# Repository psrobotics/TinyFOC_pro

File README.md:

# TinyFOC_pro

<br><br>
<br>
<br>

<br><br>

* Compact brushless motor driver modified from [mit mini cheetah driver](https://github.com/bgkatz/3phase_integrated)
* 12 bit GMR-based encoder with MA710 or AS5047p
* CAN, hardware serial

Design file exported with [Autodesk EAGLE](https://www.autodesk.com/products/eagle/overview?term=1-YEAR&tab=subscription)

## License
MIT License

## Contact
* Shuang Peng, {shuangpe}@usc.edu

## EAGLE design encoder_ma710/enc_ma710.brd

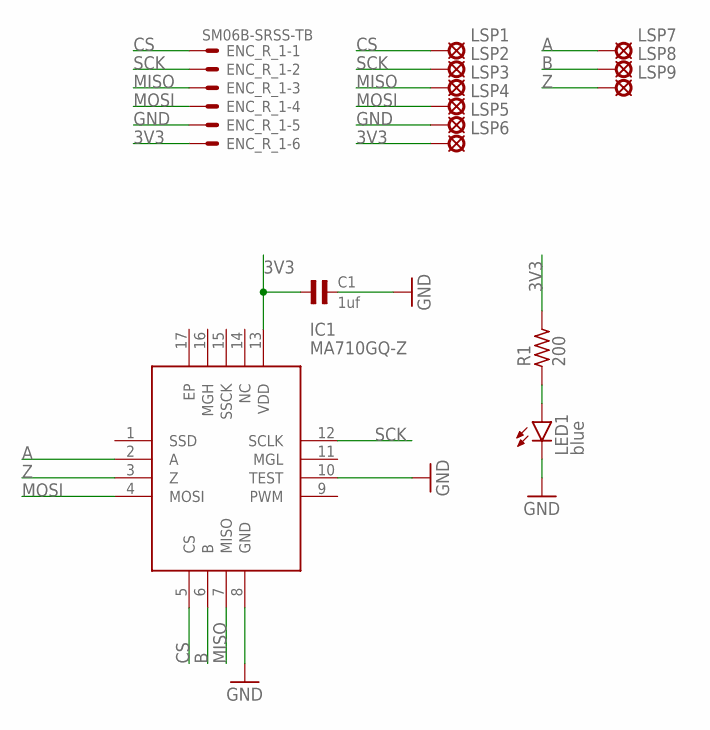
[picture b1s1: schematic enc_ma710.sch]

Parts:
C1: 1uf; 0603
ENC_R_1: SM06B-SRSS-TB
IC1: MA710GQ-Z; QFN50P300X300X100-17N
LED1: blue; SML0603
LSP1, LSP2, LSP3, LSP4, LSP5, LSP6, LSP7, LSP8, LSP9: LSP10
R1: 200; R0603

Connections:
3V3: C1.1, ENC_R_1.6, IC1.13 (VDD), LSP6.MP, R1.2
A: IC1.2 (A), LSP7.MP
B: IC1.6 (B), LSP8.MP
CS: ENC_R_1.1, IC1.5 (CS), LSP1.MP
GND: C1.2, ENC_R_1.5, IC1.8 (GND), IC1.10 (TEST), LED1.C, LSP5.MP
MISO: ENC_R_1.3, IC1.7 (MISO), LSP3.MP
MOSI: ENC_R_1.4, IC1.4 (MOSI), LSP4.MP
unnamed: LED1.A, R1.1
SCK: ENC_R_1.2, IC1.12 (SCLK), LSP2.MP
Z: IC1.3 (Z), LSP9.MP

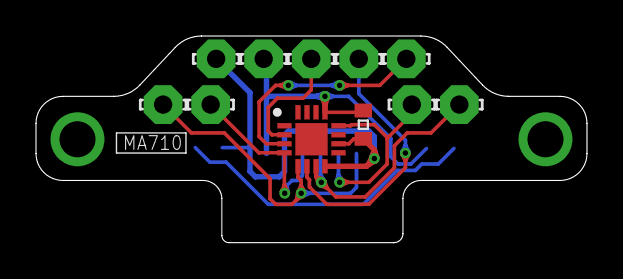
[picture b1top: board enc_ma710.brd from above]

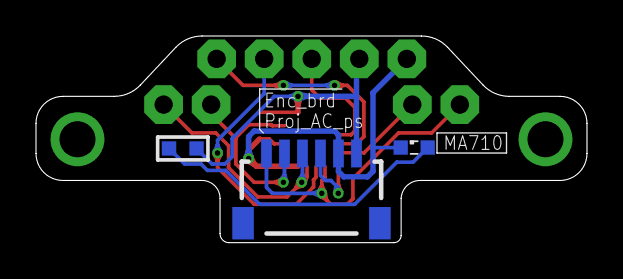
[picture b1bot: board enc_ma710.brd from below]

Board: 2 copper layers, 30.6 x 11.5 mm, 14 parts (3 on the bottom side), 10 nets.

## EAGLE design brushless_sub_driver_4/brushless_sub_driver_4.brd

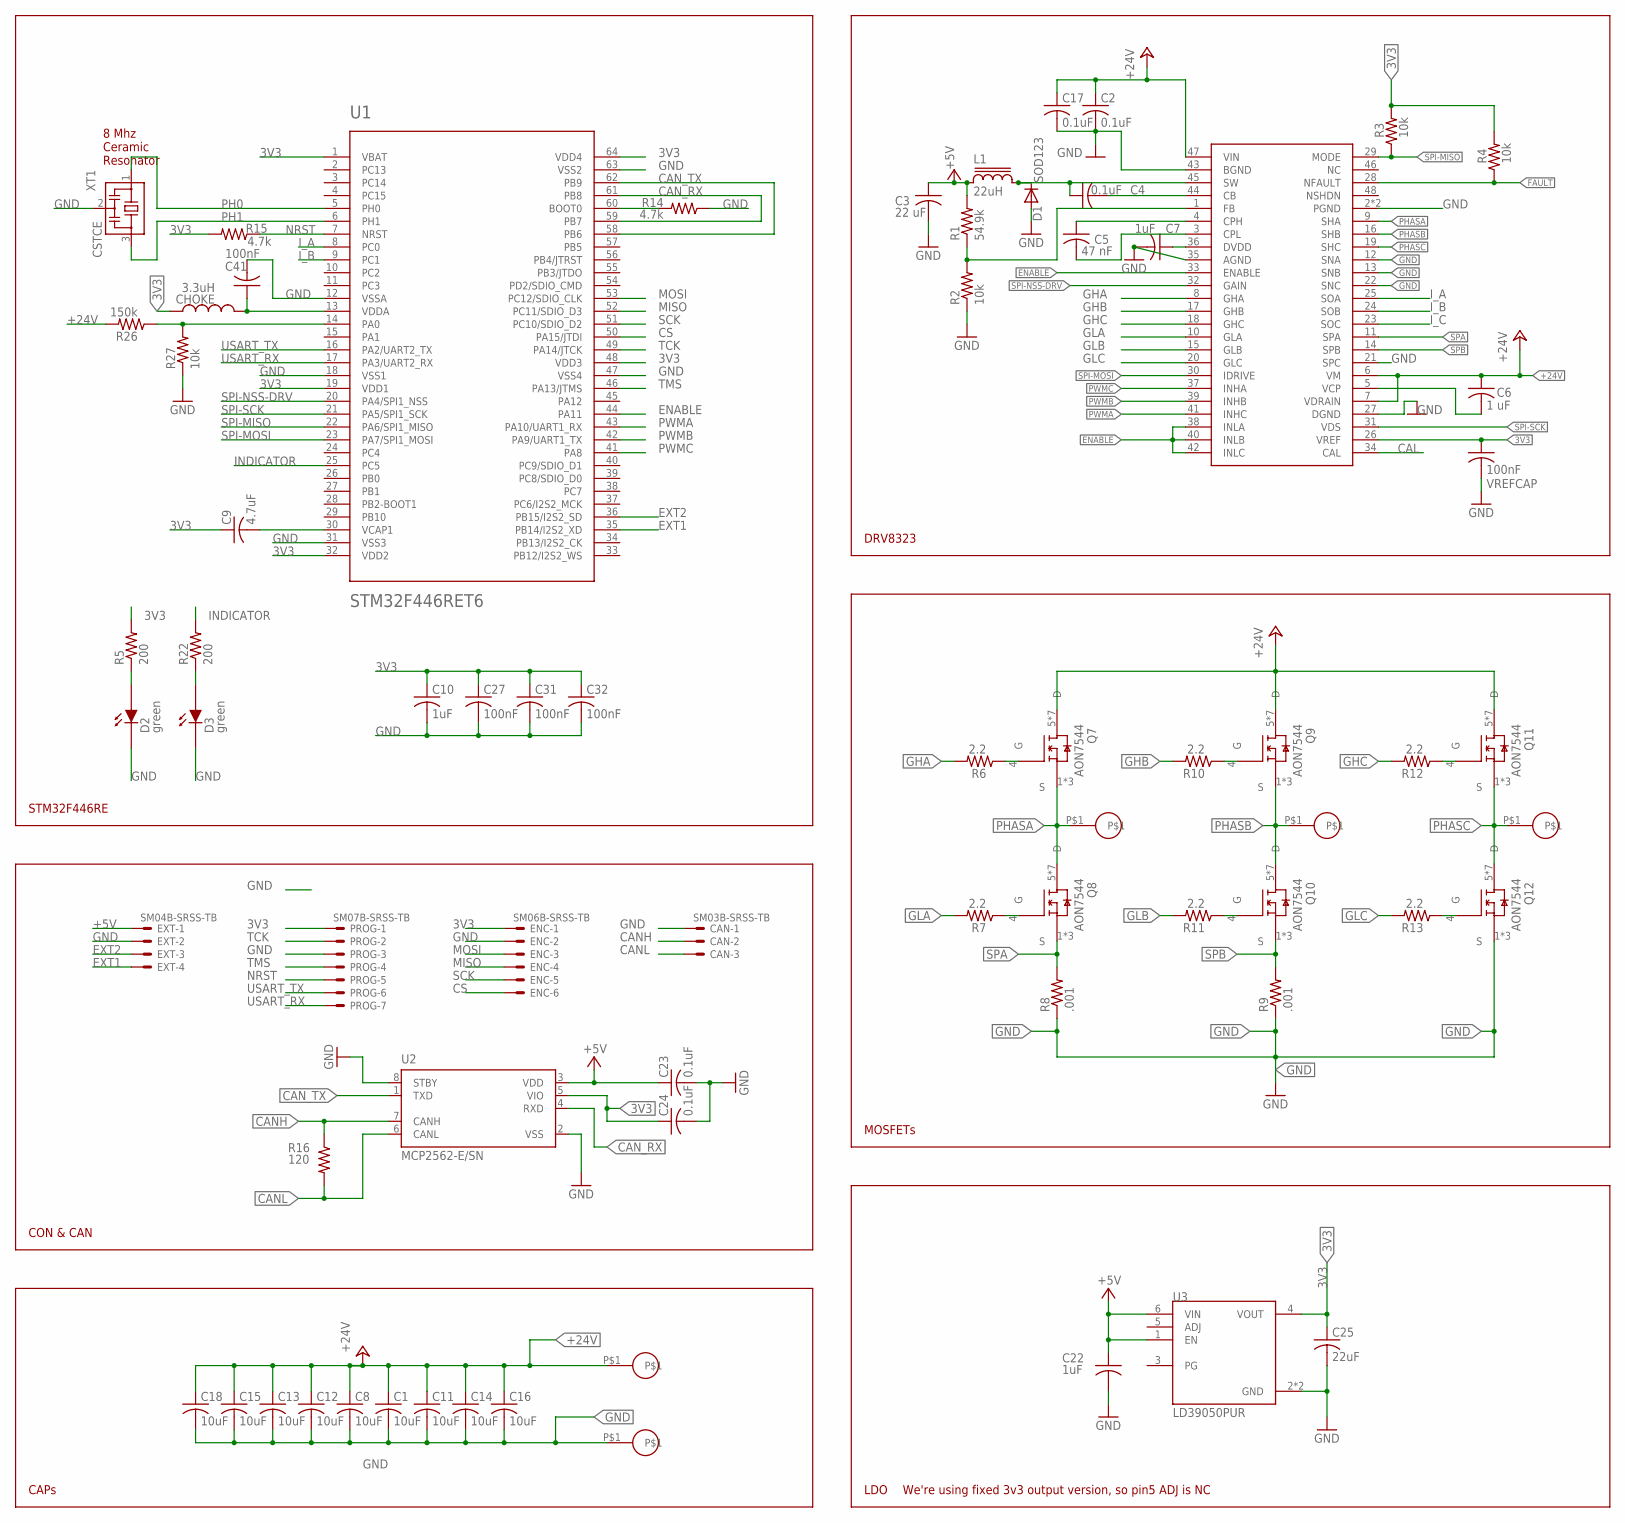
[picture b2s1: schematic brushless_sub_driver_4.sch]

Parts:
C1, C8, C11, C12, C13, C14, C15, C16, C18: 10uF; C1206K
C2, C4, C23, C24: 0.1uF; C0603K
C3: 22 uF; C0603K
C5: 47 nF; C0402K
C6: 1 uF; C0603K
C7, C10: 1uF; C0402K
C9: 4.7uF; C0402K
C17: 0.1uF; C1206K
C22: 1uF; C0402
C25: 22uF; C0603K
C27, C31, C32: 100nF; C0402K
C41: 100nF; C0402
CAN: SM03B-SRSS-TB
CHOKE: 3.3uH; 0603
D1: SOD123
D2, D3: green; 0603P
DRV1: DRV8323RH; QFN50P700X700X90-49N
ENC: SM06B-SRSS-TB
EXT: SM04B-SRSS-TB
L1: 22uH; SDR0302
O_A: 18_AWG_PAD
O_B: 18_AWG_PAD
O_C: 18_AWG_PAD
PROG: SM07B-SRSS-TB
Q7, Q8, Q9, Q10, Q11, Q12: AON7544
R1: 54.9k; R0402
R2, R3, R4, R27: 10k; R0402
R5, R22: 200; R0402
R6, R7, R10, R11, R12, R13: 2.2; R0402
R8, R9: .001; R1210
R14, R15: 4.7k; R0402
R16: 120; R0603
R26: 150k; R0402
U1: STM32F446RET6; TQFP64
U2: MCP2562-E/SN; SOIC127P600X175-8N
U3: LD39050PUR; SON95P300X300X100-7N
U$8, U$10: 18_AWG_PAD
VREFCAP: 100nF; C0402K
XT1: CSTCE

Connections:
3V3: C9.1, C10.1, C24.1, C25.1, C27.1, C31.1, C32.1, CHOKE.1, DRV1.26 (VREF), ENC.1, PROG.1, R3.2, R4.2, R5.2, R15.2, U1.1 (VBAT), U1.19 (VDD1), U1.32 (VDD2), U1.48 (VDD3), U1.64 (VDD4), U2.5 (VIO), U3.4 (VOUT), VREFCAP.1
+5V: C3.1, C22.1, C23.1, EXT.1, L1.1, R1.2, U2.3 (VDD), U3.1 (EN), U3.6 (VIN)
+24V: C1.1, C2.1, C6.1, C8.1, C11.1, C12.1, C13.1, C14.1, C15.1, C16.1, C17.1, C18.1, DRV1.6 (VM), DRV1.7 (VDRAIN), DRV1.47 (VIN), Q7.5 (D), Q7.6 (D), Q7.7 (D), Q7.8 (D), Q7.9 (D), Q7.10 (D), Q7.11 (D), Q9.5 (D), Q9.6 (D), Q9.7 (D), Q9.8 (D), Q9.9 (D), Q9.10 (D), Q9.11 (D), Q11.5 (D), Q11.6 (D), Q11.7 (D), Q11.8 (D), Q11.9 (D), Q11.10 (D), Q11.11 (D), R26.2, U$8.P$1
BOOT: C4.2, DRV1.44 (CB)
CAL: DRV1.34 (CAL)
CANH: CAN.2, R16.1, U2.7 (CANH)
CANL: CAN.3, R16.2, U2.6 (CANL)
CAN_RX: U1.59 (PB7), U1.61 (PB8), U2.4 (RXD)
CAN_TX: U1.58 (PB6), U1.62 (PB9), U2.1 (TXD)
CPH: C5.1, DRV1.4 (CPH)
CPL: C5.2, DRV1.3 (CPL)
CS: ENC.6, U1.50 (PA15/JTDI)
DEVICE3.3: C7.1, DRV1.36 (DVDD)
ENABLE: DRV1.33 (ENABLE), DRV1.38 (INLA), DRV1.40 (INLB), DRV1.42 (INLC), U1.44 (PA11)
EXT1: EXT.4, U1.35 (PB14/I2S2_XD)
EXT2: EXT.3, U1.36 (PB15/I2S2_SD)
FAULT: DRV1.28 (NFAULT), R4.1
FB: DRV1.1 (FB), R1.1, R2.2
GHA: DRV1.8 (GHA), R6.2
GHB: DRV1.17 (GHB), R10.2
GHC: DRV1.18 (GHC), R12.2
GLA: DRV1.10 (GLA), R7.2
GLB: DRV1.15 (GLB), R11.2
GLC: DRV1.20 (GLC), R13.2
GND: C1.2, C2.2, C3.2, C7.2, C8.2, C10.2, C11.2, C12.2, C13.2, C14.2, C15.2, C16.2, C17.2, C18.2, C22.2, C23.2, C24.2, C25.2, C27.2, C31.2, C32.2, C41.2, CAN.1, D1.A, D2.2 (D_OUT), D3.2 (D_OUT), DRV1.2 (PGND), DRV1.12 (SNA), DRV1.13 (SNB), DRV1.21 (SPC), DRV1.22 (SNC), DRV1.27 (DGND), DRV1.35 (AGND), DRV1.43 (BGND), DRV1.49 (PGND), ENC.2, EXT.2, PROG.3, Q12.1 (S), Q12.2 (S), Q12.3 (S), R2.1, R8.1, R9.1, R14.1, R27.1, U1.12 (VSSA), U1.18 (VSS1), U1.31 (VSS3), U1.47 (VSS4), U1.63 (VSS2), U2.2 (VSS), U2.8 (STBY), U3.2 (GND), U3.7 (GND), U$10.P$1, VREFCAP.2, XT1.2
INDICATOR: R22.2, U1.25 (PC5)
I_A: DRV1.25 (SOA), U1.8 (PC0)
I_B: DRV1.24 (SOB), U1.9 (PC1)
I_C: DRV1.23 (SOC)
MISO: ENC.4, U1.52 (PC11/SDIO_D3)
MOSI: ENC.3, U1.53 (PC12/SDIO_CLK)
unnamed: D2.1 (D_IN), R5.1
unnamed: C41.1, CHOKE.2, U1.13 (VDDA)
unnamed: C9.2, U1.30 (VCAP1)
unnamed: Q7.4 (G), R6.1
unnamed: Q8.4 (G), R7.1
unnamed: Q9.4 (G), R10.1
unnamed: Q10.4 (G), R11.1
unnamed: Q11.4 (G), R12.1
unnamed: Q12.4 (G), R13.1
unnamed: R14.2, U1.60 (BOOT0)
unnamed: R26.1, R27.2, U1.14 (PA0)
unnamed: D3.1 (D_IN), R22.1
NRST: PROG.5, R15.1, U1.7 (NRST)
PH0: U1.5 (PH0), XT1.1
PH1: U1.6 (PH1), XT1.3
PHASA: DRV1.9 (SHA), O_A.P$1, Q7.1 (S), Q7.2 (S), Q7.3 (S), Q8.5 (D), Q8.6 (D), Q8.7 (D), Q8.8 (D), Q8.9 (D), Q8.10 (D), Q8.11 (D)
PHASB: DRV1.16 (SHB), O_B.P$1, Q9.1 (S), Q9.2 (S), Q9.3 (S), Q10.5 (D), Q10.6 (D), Q10.7 (D), Q10.8 (D), Q10.9 (D), Q10.10 (D), Q10.11 (D)
PHASC: DRV1.19 (SHC), O_C.P$1, Q11.1 (S), Q11.2 (S), Q11.3 (S), Q12.5 (D), Q12.6 (D), Q12.7 (D), Q12.8 (D), Q12.9 (D), Q12.10 (D), Q12.11 (D)
PWMA: DRV1.41 (INHC), U1.43 (PA10/UART1_RX)
PWMB: DRV1.39 (INHB), U1.42 (PA9/UART1_TX)
PWMC: DRV1.37 (INHA), U1.41 (PA8)
SCK: ENC.5, U1.51 (PC10/SDIO_D2)
SPA: DRV1.11 (SPA), Q8.1 (S), Q8.2 (S), Q8.3 (S), R8.2
SPB: DRV1.14 (SPB), Q10.1 (S), Q10.2 (S), Q10.3 (S), R9.2
SPI-MISO: DRV1.29 (MODE), R3.1, U1.22 (PA6/SPI1_MISO)
SPI-MOSI: DRV1.30 (IDRIVE), U1.23 (PA7/SPI1_MOSI)
SPI-NSS-DRV: DRV1.32 (GAIN), U1.20 (PA4/SPI1_NSS)
SPI-SCK: DRV1.31 (VDS), U1.21 (PA5/SPI1_SCK)
SW: C4.1, D1.C, DRV1.45 (SW), L1.2
TCK: PROG.2, U1.49 (PA14/JTCK)
TMS: PROG.4, U1.46 (PA13/JTMS)
USART_RX: PROG.7, U1.17 (PA3/UART2_RX)
USART_TX: PROG.6, U1.16 (PA2/UART2_TX)
VCP: C6.2, DRV1.5 (VCP)

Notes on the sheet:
STM32F446RE
DRV8323
MOSFETs
LDO
CAPs
CON & CAN
8 Mhz Ceramic Resonator
We're using fixed 3v3 output version, so pin5 ADJ is NC

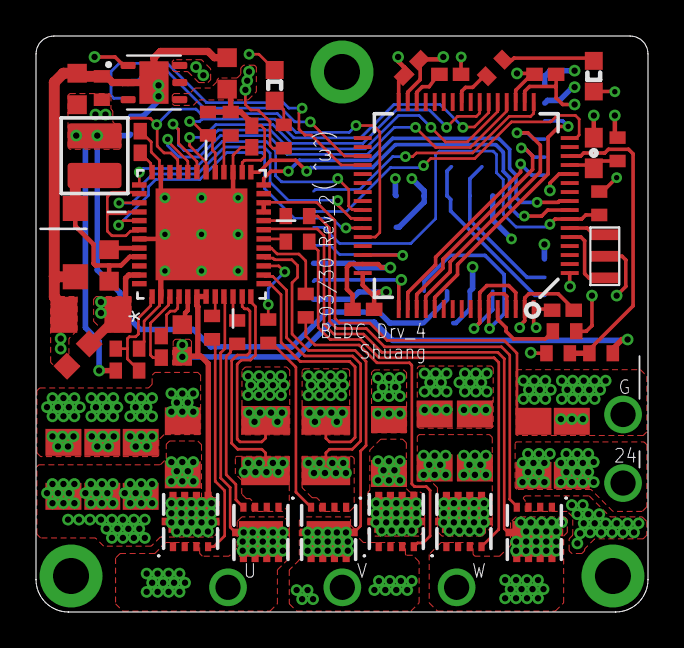
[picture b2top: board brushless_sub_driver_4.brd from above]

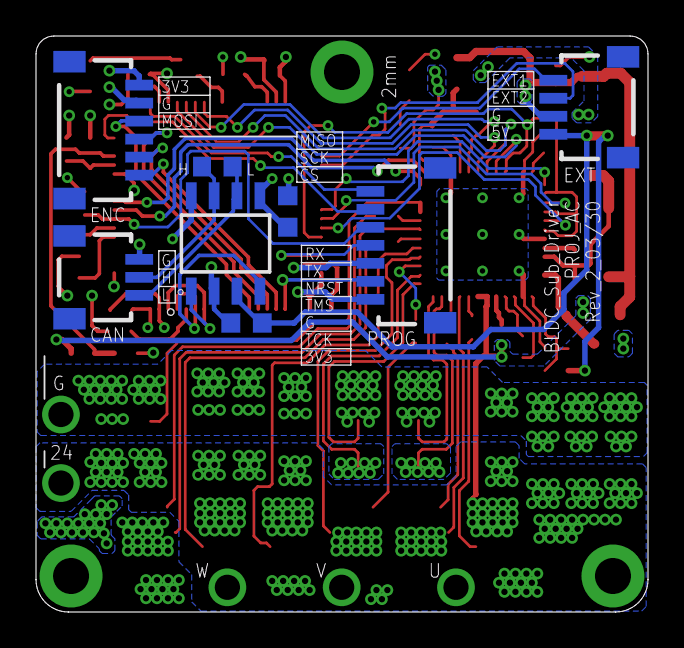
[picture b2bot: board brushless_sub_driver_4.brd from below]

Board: 4 copper layers, 34.0 x 32.0 mm, 71 parts (8 on the bottom side), 63 nets.

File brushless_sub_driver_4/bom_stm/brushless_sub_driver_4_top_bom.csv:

Comment,Designator,Footprint,LCSC Part #
.001,R8 R9,R1210,
0.1uF,C2 C4,C0603K,
0.1uF,C17,C1206K,
1 uF,C6,C0603K,
1uF,C7 C10,C0402K,
1uF,C22,C0402,
2.2,R6 R7 R10 R11 R12 R13,R0402,
3.3uH,CHOKE,0603,
4.7k,R14 R15,R0402,
4.7uF,C9,C0402K,
10k,R2 R3 R4 R27,R0402,
10uF,C1 C8 C11 C12 C13 C14 C15 C16 C18,C1206K,
22 uF,C3,C0603K,
22uF,C25,C0603K,
22uH,L1,SDR0302,
47 nF,C5,C0402K,
54.9k,R1,R0402,
100nF,C27 C31 C32,C0402K,
100nF,C41,C0402,
100nF,VREFCAP,C0402K,
150k,R26,R0402,
200,R5 R22,R0402,
AON7544,Q7 Q8 Q9 Q10 Q11 Q12,AON7544,
CSTCE,XT1,CSTCE,
DRV8323RH,DRV1,QFN50P700X700X90-49N,
LD39050PUR,U3,SON95P300X300X100-7N,
SOD123,D1,SOD123,
STM32F446RET6,U1,TQFP64,
green,D2 D3,0603P,

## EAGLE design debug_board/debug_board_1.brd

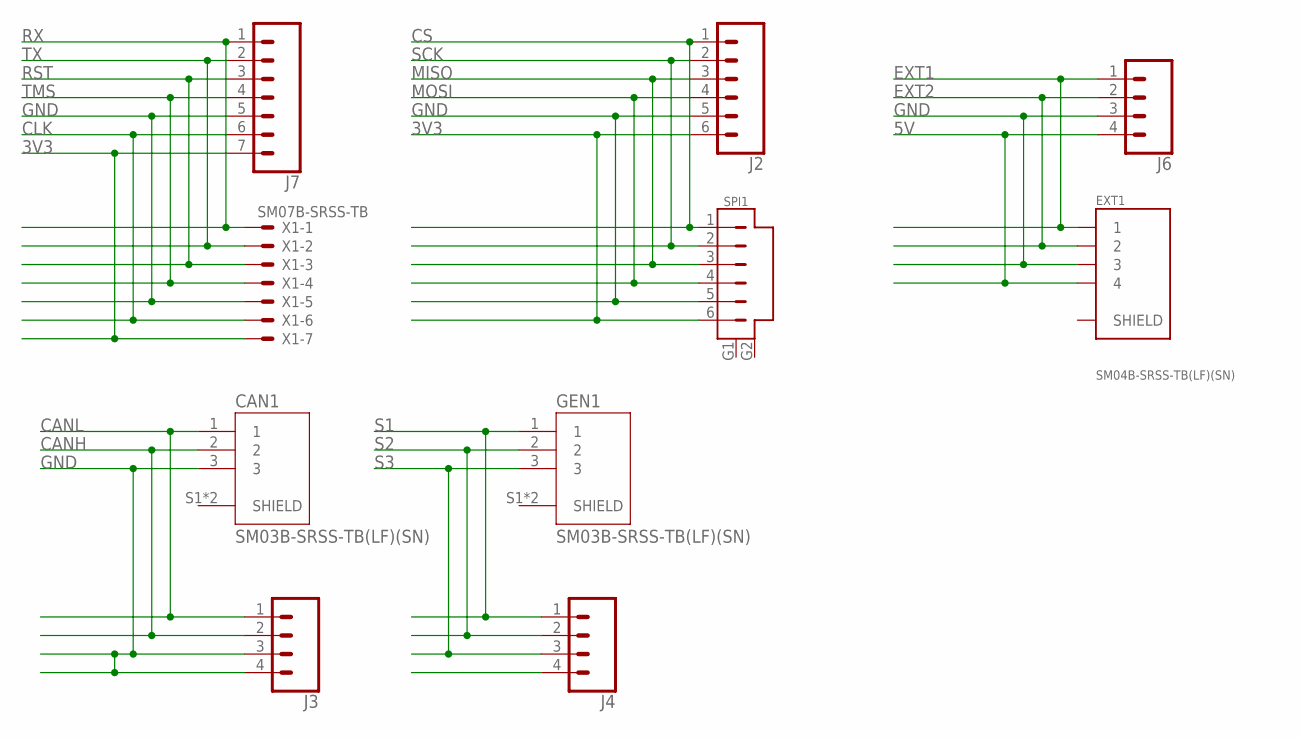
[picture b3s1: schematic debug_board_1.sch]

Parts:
CAN1: SM03B-SRSS-TB(LF)(SN); JST_SM03B-SRSS-TB(LF)(SN)
EXT1: SM04B-SRSS-TB(LF)(SN); JST_SM04B-SRSS-TB(LF)(SN)
GEN1: SM03B-SRSS-TB(LF)(SN); JST_SM03B-SRSS-TB(LF)(SN)
J2: CONN_06LONGPADS; 1X06_LONGPADS
J3, J4, J6: CONN_04LONGPADS; 1X04_LONGPADS
J7: CONN_07LONGPADS; 1X07_LONGPADS
SPI1: SM06B-SRSS-TB; SM06B
X1: SM07B-SRSS-TB

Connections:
3V3: J2.6, J7.7, SPI1.6, X1.7
5V: EXT1.4, J6.4
CANH: CAN1.2, J3.2
CANL: CAN1.1, J3.1
CLK: J7.6, X1.6
CS: J2.1, SPI1.1
EXT1: EXT1.1, J6.1
EXT2: EXT1.2, J6.2
GND: CAN1.3, EXT1.3, J2.5, J3.3, J3.4, J6.3, J7.5, SPI1.5, X1.5
MISO: J2.3, SPI1.3
MOSI: J2.4, SPI1.4
RST: J7.3, X1.3
RX: J7.1, X1.1
S1: GEN1.1, J4.1
S2: GEN1.2, J4.2
S3: GEN1.3, J4.3
SCK: J2.2, SPI1.2
TMS: J7.4, X1.4
TX: J7.2, X1.2

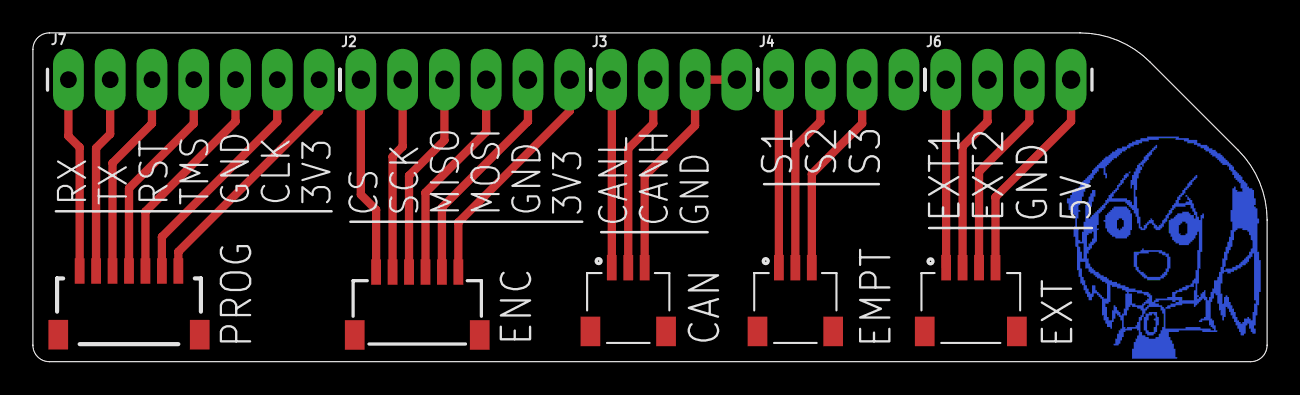
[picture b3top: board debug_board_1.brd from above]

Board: 2 copper layers, 75.0 x 20.0 mm, 11 parts (0 on the bottom side), 19 nets.

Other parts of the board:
U$1: SODAYO_1

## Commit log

2024-02-24 add: 0224 init
2024-02-27 add: 0227 vid

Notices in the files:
parts and their libraries:
SparkFun-Passives: Licensing: Creative Commons ShareAlike 4.0 International - https://creativecommons.org/licenses/by-sa/4.0
inductor-bourns: Copyright (C) 2008, Bob Starr
m-pad-2.1: License : GNU General Public License version 2 (see bottom)
rc-master-smd: Copyright (C) 2007, Bob Starr
